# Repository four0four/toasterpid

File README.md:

# toasterpid

Firmware for my reflow oven PID controller (WIP!)

## Complete:
+ Simple serial driver
+ Thermocouple driver
+ LCD driver (4-bit, 8-bit)

## Work in progress:
+ PID algorithm/tuning
  + PID values don't differ much from 0 or 255, and given the oven's thermal momentum, they shouldn't...
+ Testing: Insulation in the oven

## Entirely untouched:
+ User interface

## Potential features:
+ USB instead of serial (final version will use an atmega16u4 or similar)
+ Serial (or USB) control

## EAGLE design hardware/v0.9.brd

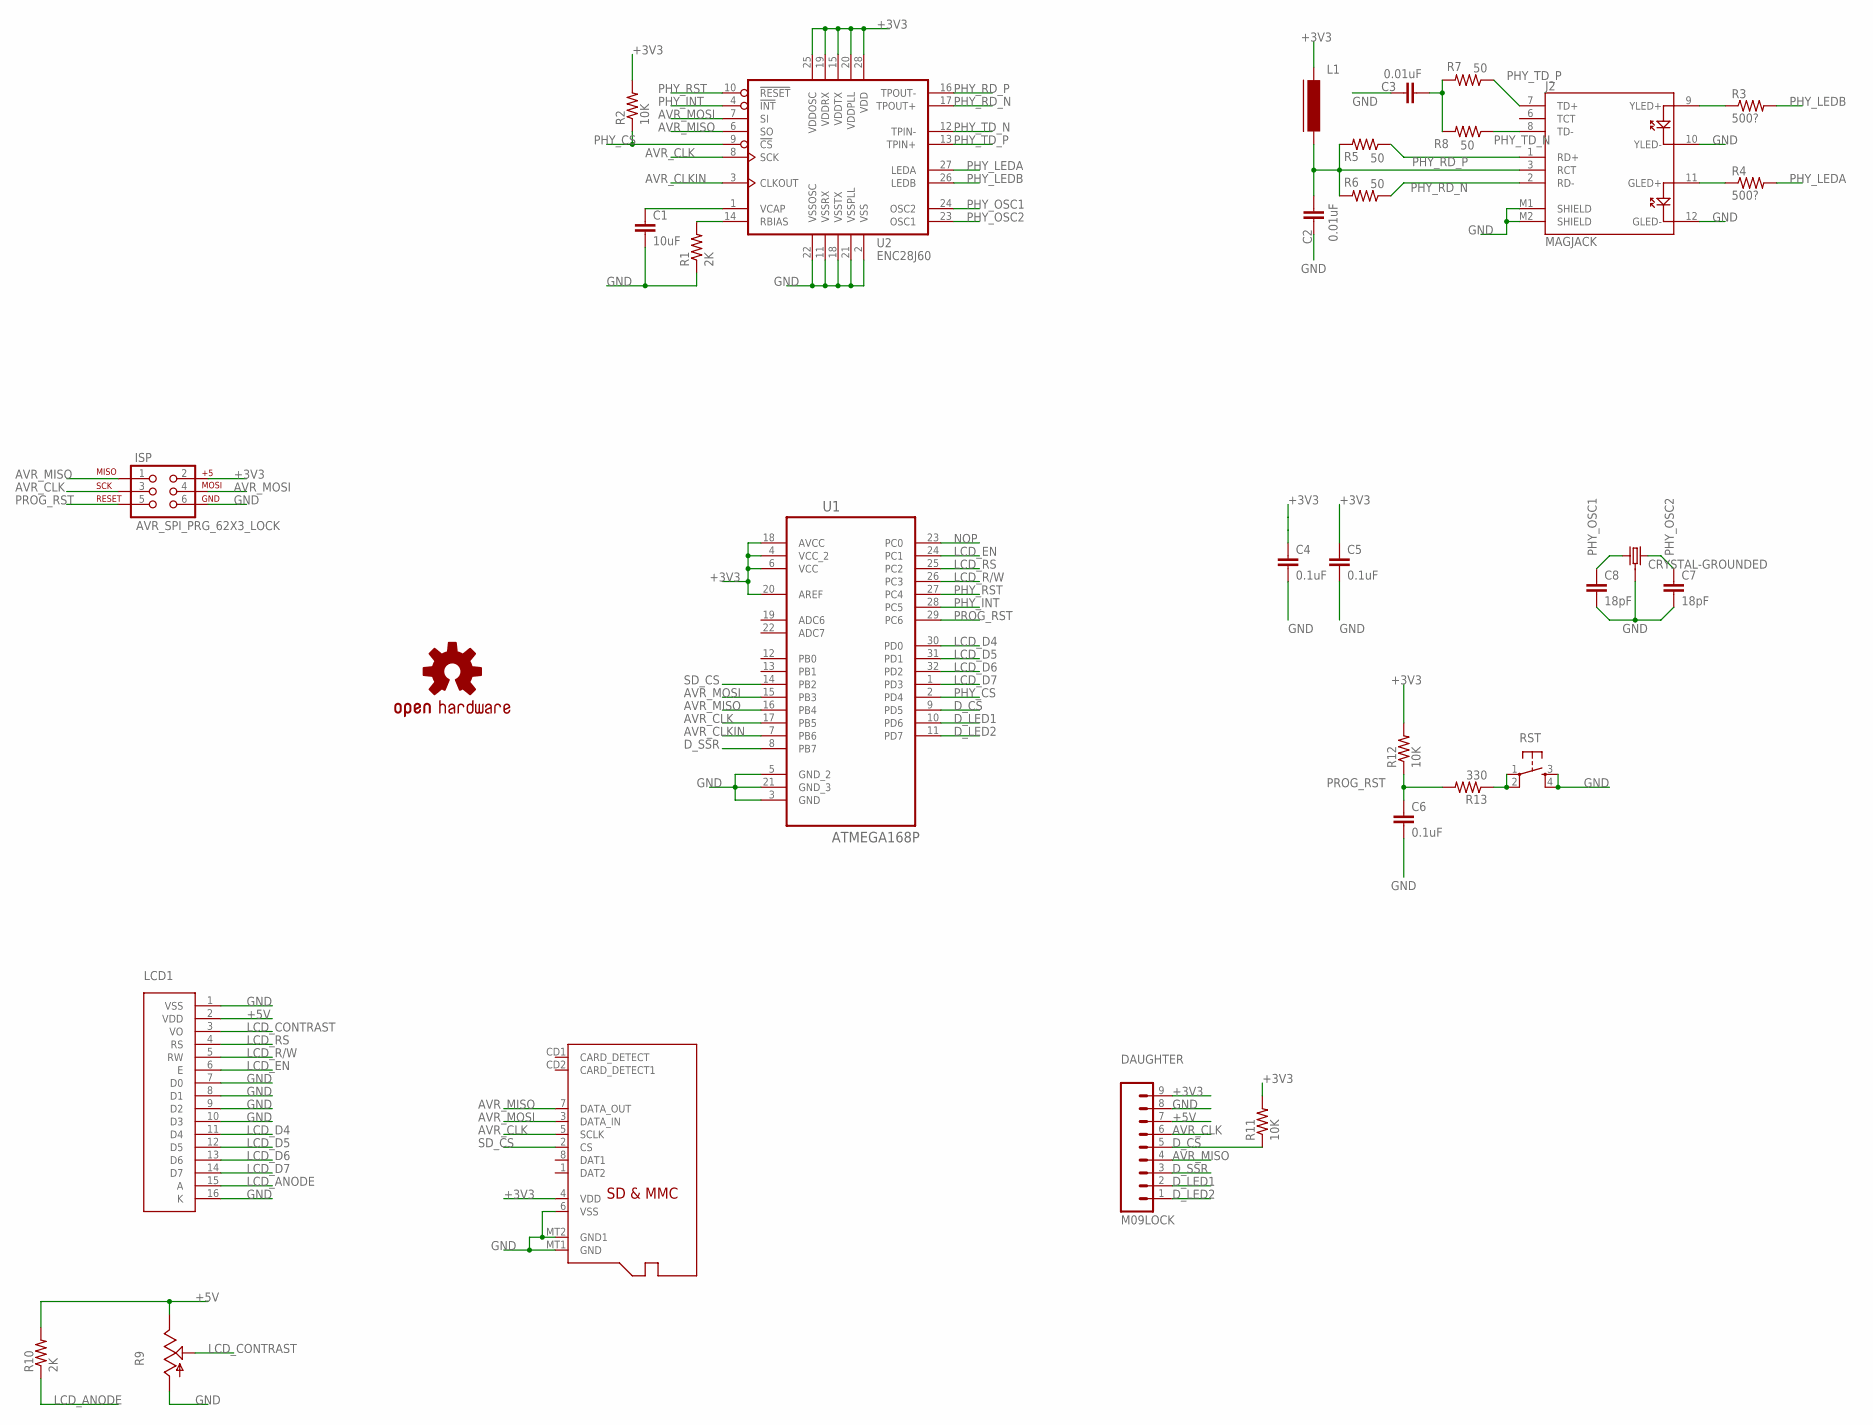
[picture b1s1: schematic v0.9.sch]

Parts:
C1: 10uF; 0603-CAP
C2, C3: 0.01uF; 0603-CAP
C4, C5: 0.1uF; 0402-CAP
C6: 0.1uF; 0603-CAP
C7, C8: 18pF; 0402-CAP
DAUGHTER: M09LOCK; 1X09_LOCK
ISP: AVR_SPI_PRG_62X3_LOCK; 2X3_LOCK
J2: MAGJACK
L1: FERRITE-0603; FB603
LCD1: HD44780; .1"16PIN
LOGO1: OSHW-LOGOS; OSHW-LOGO-S
R1, R10: 2K; 0603-RES
R2, R11, R12: 10K; 0603-RES
R3, R4: 500?; 0603-RES
R5, R6, R7, R8: 50; 0603-RES
R9: TRIM_US-B64Y; B64Y
R13: 330; 0603-RES
RST: TAC_SWITCHSMD; TACTILE-SWITCH-SMD
SD: MICROSD
U1: ATMEGA168P; QFP80P900X900X120-32N
U2: ENC28J60; SOIC-28W
Y1: CRYSTAL-GROUNDED; CRYSTAL-SMD-5X3

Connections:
+3V3: C4.1, C5.1, DAUGHTER.9, ISP.2, L1.1, R2.2, R11.2, R12.2, SD.4 (VDD), U1.4 (VCC_2), U1.6 (VCC), U1.18 (AVCC), U1.20 (AREF), U2.15 (VDDTX), U2.19 (VDDRX), U2.20 (VDDPLL), U2.25 (VDDOSC), U2.28 (VDD)
+5V: DAUGHTER.7, LCD1.2 (VDD), R9.E, R10.2
AVR_CLK: DAUGHTER.6, ISP.3, SD.5 (SCLK), U1.17 (PB5), U2.8 (SCK)
AVR_CLKIN: U1.7 (PB6), U2.3 (CLKOUT)
AVR_MISO: DAUGHTER.4, ISP.1, SD.7 (DATA_OUT), U1.16 (PB4), U2.6 (SO)
AVR_MOSI: ISP.4, SD.3 (DATA_IN), U1.15 (PB3), U2.7 (SI)
D_CS: DAUGHTER.5, R11.1, U1.9 (PD5)
D_LED1: DAUGHTER.2, U1.10 (PD6)
D_LED2: DAUGHTER.1, U1.11 (PD7)
D_SSR: DAUGHTER.3, U1.8 (PB7)
GND: C1.2, C2.1, C3.1, C4.2, C5.2, C6.2, C7.2, C8.2, DAUGHTER.8, ISP.6, J2.10 (YLED-), J2.12 (GLED-), J2.M1 (SHIELD), J2.M2 (SHIELD), LCD1.1 (VSS), LCD1.7 (D0), LCD1.8 (D1), LCD1.9 (D2), LCD1.10 (D3), LCD1.16 (K), R1.1, R9.A, RST.3, RST.4, SD.6 (VSS), SD.MT1 (GND), SD.MT2 (GND1), U1.3 (GND), U1.5 (GND_2), U1.21 (GND_3), U2.2 (VSS), U2.11 (VSSRX), U2.18 (VSSTX), U2.21 (VSSPLL), U2.22 (VSSOSC), Y1.2 (3), Y1.4 (3)
LCD_ANODE: LCD1.15 (A), R10.1
LCD_CONTRAST: LCD1.3 (VO), R9.S
LCD_D4: LCD1.11 (D4), U1.30 (PD0)
LCD_D5: LCD1.12 (D5), U1.31 (PD1)
LCD_D6: LCD1.13 (D6), U1.32 (PD2)
LCD_D7: LCD1.14 (D7), U1.1 (PD3)
LCD_EN: LCD1.6 (E), U1.24 (PC1)
LCD_R/W: LCD1.5 (RW), U1.26 (PC3)
LCD_RS: LCD1.4 (RS), U1.25 (PC2)
unnamed: J2.11 (GLED+), R4.1
unnamed: J2.9 (YLED+), R3.1
unnamed: R13.1, RST.1, RST.2
unnamed: C1.1, U2.1 (VCAP)
unnamed: R1.2, U2.14 (RBIAS)
NOP: U1.23 (PC0)
PHY_CS: R2.1, U1.2 (PD4), U2.9 (!CS)
PHY_INT: U1.28 (PC5), U2.4 (!INT)
PHY_LEDA: R4.2, U2.27 (LEDA)
PHY_LEDB: R3.2, U2.26 (LEDB)
PHY_OSC1: C8.1, U2.24 (OSC2), Y1.3 (1)
PHY_OSC2: C7.1, U2.23 (OSC1), Y1.1 (2)
PHY_RD_N: J2.2 (RD-), R6.1, U2.17 (TPOUT+)
PHY_RD_P: J2.1 (RD+), R5.1, U2.16 (TPOUT-)
PHY_RST: U1.27 (PC4), U2.10 (!RESET)
PHY_TD_N: J2.8 (TD-), R8.1, U2.12 (TPIN-)
PHY_TD_P: J2.7 (TD+), R7.1, U2.13 (TPIN+)
PROG_RST: C6.1, ISP.5, R12.1, R13.2, U1.29 (PC6)
RCT: C2.2, J2.3 (RCT), L1.2, R5.2, R6.2
SD_CS: SD.2 (CS), U1.14 (PB2)
TDCAP: C3.2, R7.2, R8.2

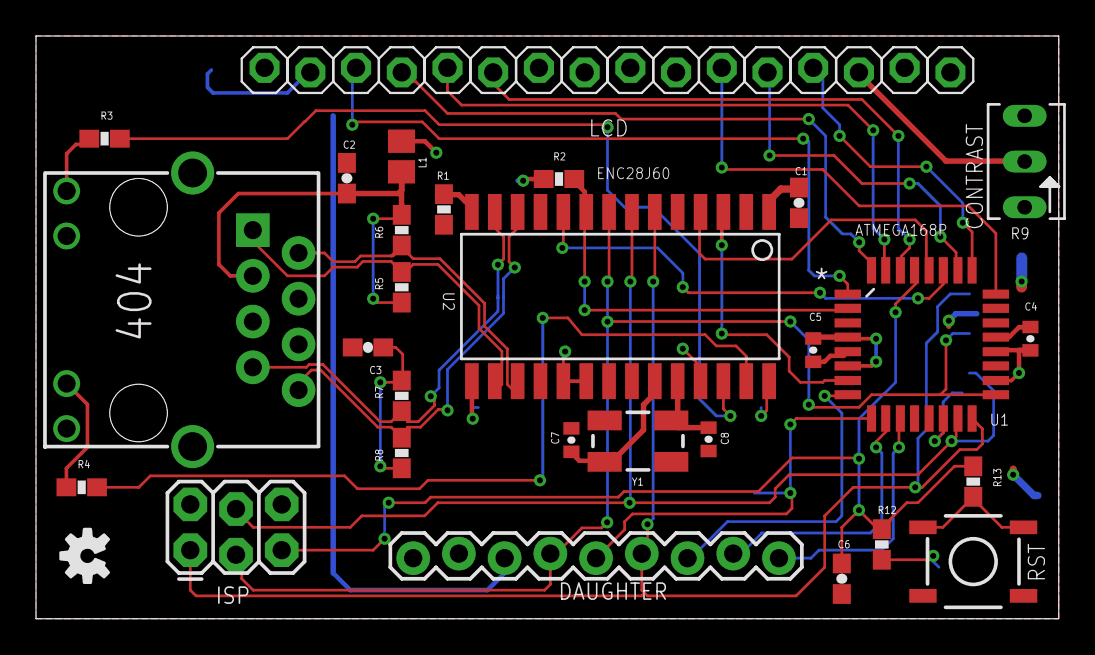
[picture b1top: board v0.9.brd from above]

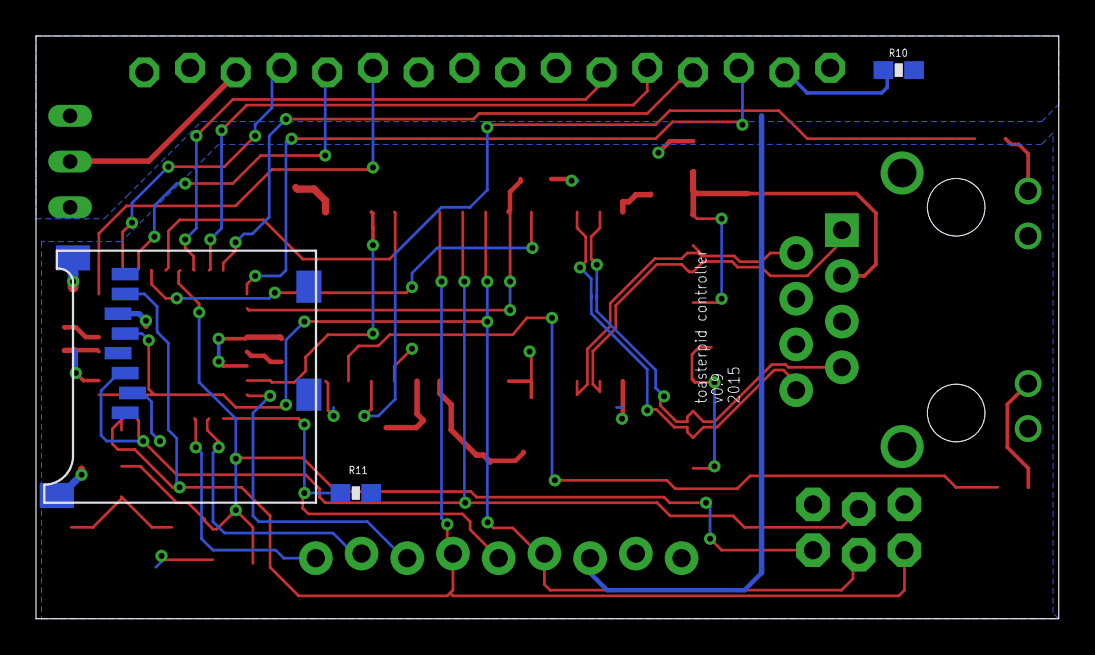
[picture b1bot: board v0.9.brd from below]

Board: 2 copper layers, 56.8 x 32.4 mm, 32 parts (3 on the bottom side), 40 nets.

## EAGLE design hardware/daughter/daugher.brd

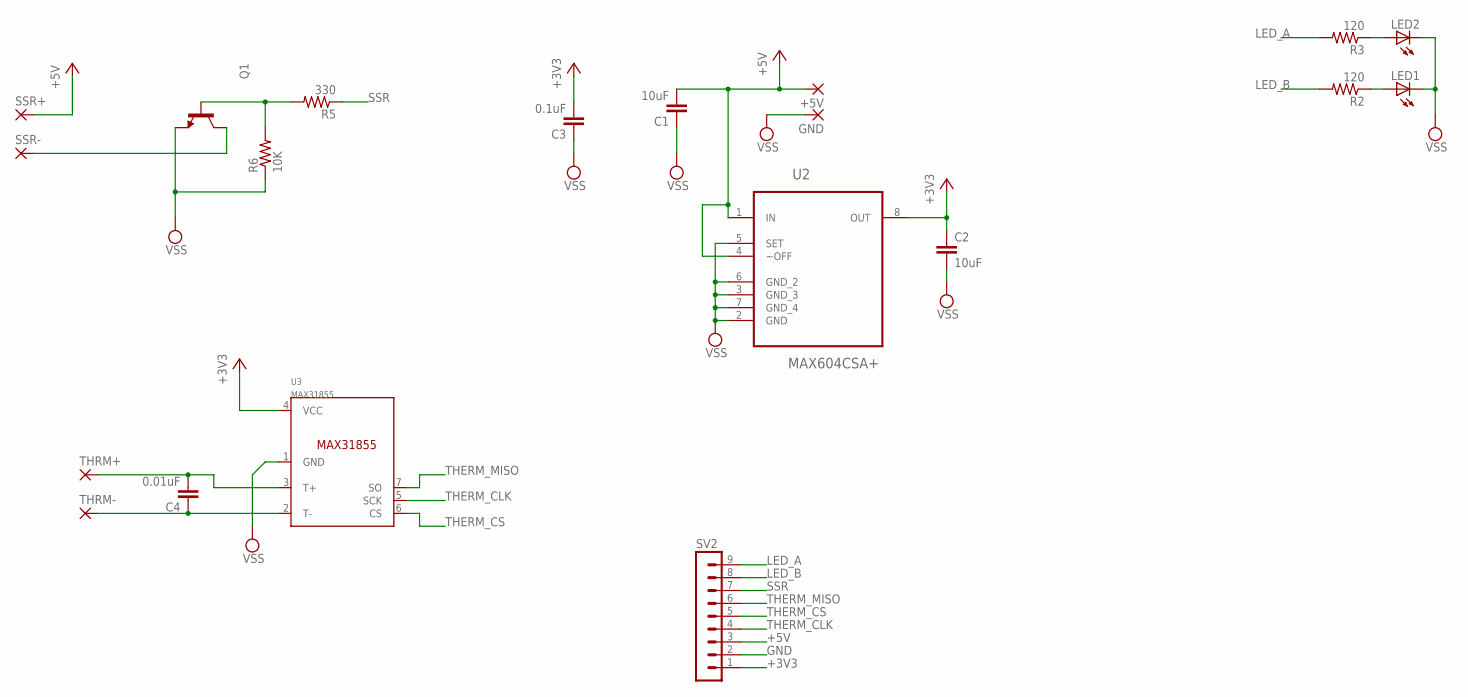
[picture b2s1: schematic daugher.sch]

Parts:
+5V: 1,6/0,8
C1, C2: 10uF; C0603
C3: 0.1uF; C0603
C4: 0.01uF; C0603
GND: 1,6/0,8
LED1, LED2: LEDCHIP-LED0805; CHIP-LED0805
Q1: BC849SMD; SOT23-BEC
R2, R3: 120; R0603
R5: 330; R0603
R6: 10K; R0603
SSR+: 1,6/0,8
SSR-: 1,6/0,8
SV2: MA09-1
THRM+: 1,6/0,8
THRM-: 1,6/0,8
U2: MAX604CSA+; SOIC127P600X175-8N
U3: MAX31855; SOIC8

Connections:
+3V3: C2.1, C3.2, SV2.1, U2.8 (OUT), U3.4 (VCC)
+5V: +5V.1, C1.2, SSR+.1, SV2.3, U2.1 (IN), U2.4 (~OFF)
GND: C1.1, C3.1, GND.1, LED1.C, LED2.C, Q1.E, R6.1, SV2.2, U2.2 (GND), U2.3 (GND_3), U2.5 (SET), U2.6 (GND_2), U2.7 (GND_4), U3.1 (GND)
GND1: Q1.C, SSR-.1
LED_A: R3.2, SV2.9
LED_B: R2.2, SV2.8
unnamed: C4.1, THRM-.1, U3.2 (T-)
unnamed: C4.2, THRM+.1, U3.3 (T+)
unnamed: LED1.A, R2.1
unnamed: LED2.A, R3.1
unnamed: Q1.B, R5.2, R6.2
SSR: R5.1, SV2.7
THERM_CLK: SV2.4, U3.5 (SCK)
THERM_CS: SV2.5, U3.6 (CS)
THERM_MISO: SV2.6, U3.7 (SO)
VSS: C2.2

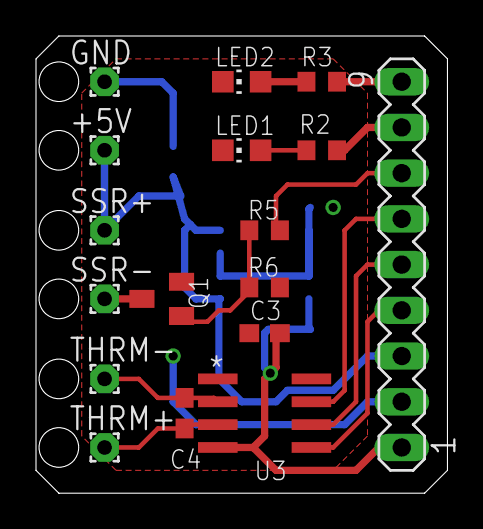
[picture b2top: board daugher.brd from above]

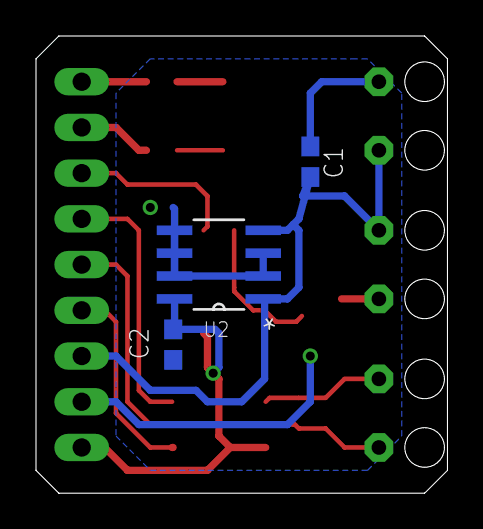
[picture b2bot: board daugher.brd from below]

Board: 2 copper layers, 22.9 x 25.4 mm, 20 parts (3 on the bottom side), 15 nets.

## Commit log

2013-07-12 barebones - working on HD44780 code
2013-07-26 basic lcd communication code. no init yet
2013-07-29 rewrote LCD drive. damn thing still isn't right
2013-08-30 preliminary thermocouple amp driver [untested]
2013-09-03 s/getInternalTemp/getInternetTemp/ ....
2013-09-09 minor documentation and housekeeping. pending testing
2013-09-28 cleaning, initial serial
2013-10-02 makefile rework, gitignore update, serial being irritating
2013-10-02 .data sections are a shame to waste. makefile issue resolved.
2013-10-02 added master source file and makefile
2013-10-03 functional thermocouple amplifier code - messy
2013-11-12 partial commit - untested code everywhere
2013-11-12 Added some debug info to make flash
2013-11-12 LCD working, external temp measurement working
2013-11-12 cleaned up/optimized code. added RW bit support and write abstractions.
2013-11-13 Added proper newline and overflow (into max of 32ch) support to LCD driver
2013-11-14 Added per-line support - to be used for menu-driven UI
2013-11-15 working on thermocouple decoding, added roadmap
2013-11-24 changed test program
2013-11-24 forgot to check LCDBUSY bit on generic write, removed cludgy delay as result
2013-11-26 Cleaned up
2014-01-05 minor updates, started work on PID. added tick/interrupt
2014-01-06 added interpolation functions, reluctantly using floating point for now...
2014-01-06 PID added. TODO: clean up
2014-01-07 removed lcd cursor in init
2014-01-07 time source stability issues -> temporary ceiling value hack
2014-01-07 overhauled target temp functionality. need to write PID function.
2014-01-07 fixed timer compare value
2014-01-07 cleaned up lcd test
2014-01-07 internal read update
2014-01-13 added 4 bit wide lcd driver
2014-01-13 fixed corner case with newlines
2014-01-13 changes sitting in vim's buffer...
2014-01-13 moved toasterpid to a 4 bit LCD bus
2014-01-14 updated roadmap and README
2014-06-29 added schematic/board eagle files
2014-07-11 Fixed tx diff pair impedence matching (hardware)
2014-07-11 routed correct (upper) 4 bit lcd bus (hardware)
2014-07-11 fixed last commit (hardware)
2015-02-18 fooled around with timing, etc
2015-02-18 new hardware revision
2015-02-18 fixed roadmap md
2015-02-18 added pin listing for the mcu
2015-05-22 initial bare-bones sd
2015-05-22 fixed compilation errors in sd driver
2015-05-25 cleaned up main makefile
2015-05-25 current board revision config updates
2015-05-26 4 bit rework
2016-01-27 dev in master. merging a lot of stuff
2016-01-27 current sdcard code is utter trash, keeping this until rewritten. unfunctional.
2016-01-27 don't use trashy sd code
2016-01-27 ethernet start

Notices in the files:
parts and their libraries:
SparkFun-Connectors: Licensing: Creative Commons ShareAlike 4.0 International - https://creativecommons.org/licenses/by-sa/4.0
